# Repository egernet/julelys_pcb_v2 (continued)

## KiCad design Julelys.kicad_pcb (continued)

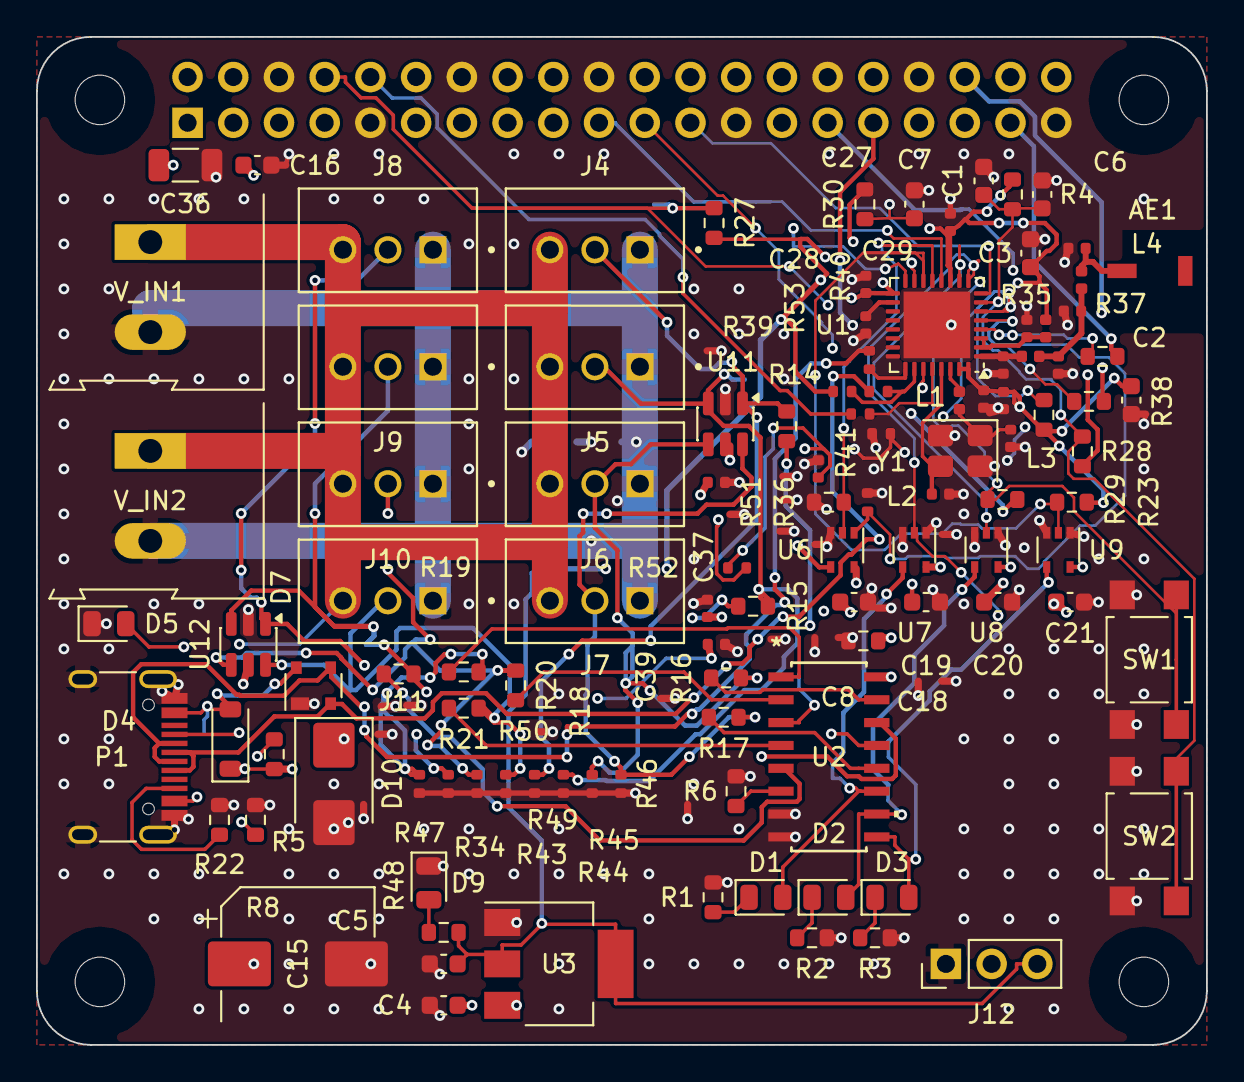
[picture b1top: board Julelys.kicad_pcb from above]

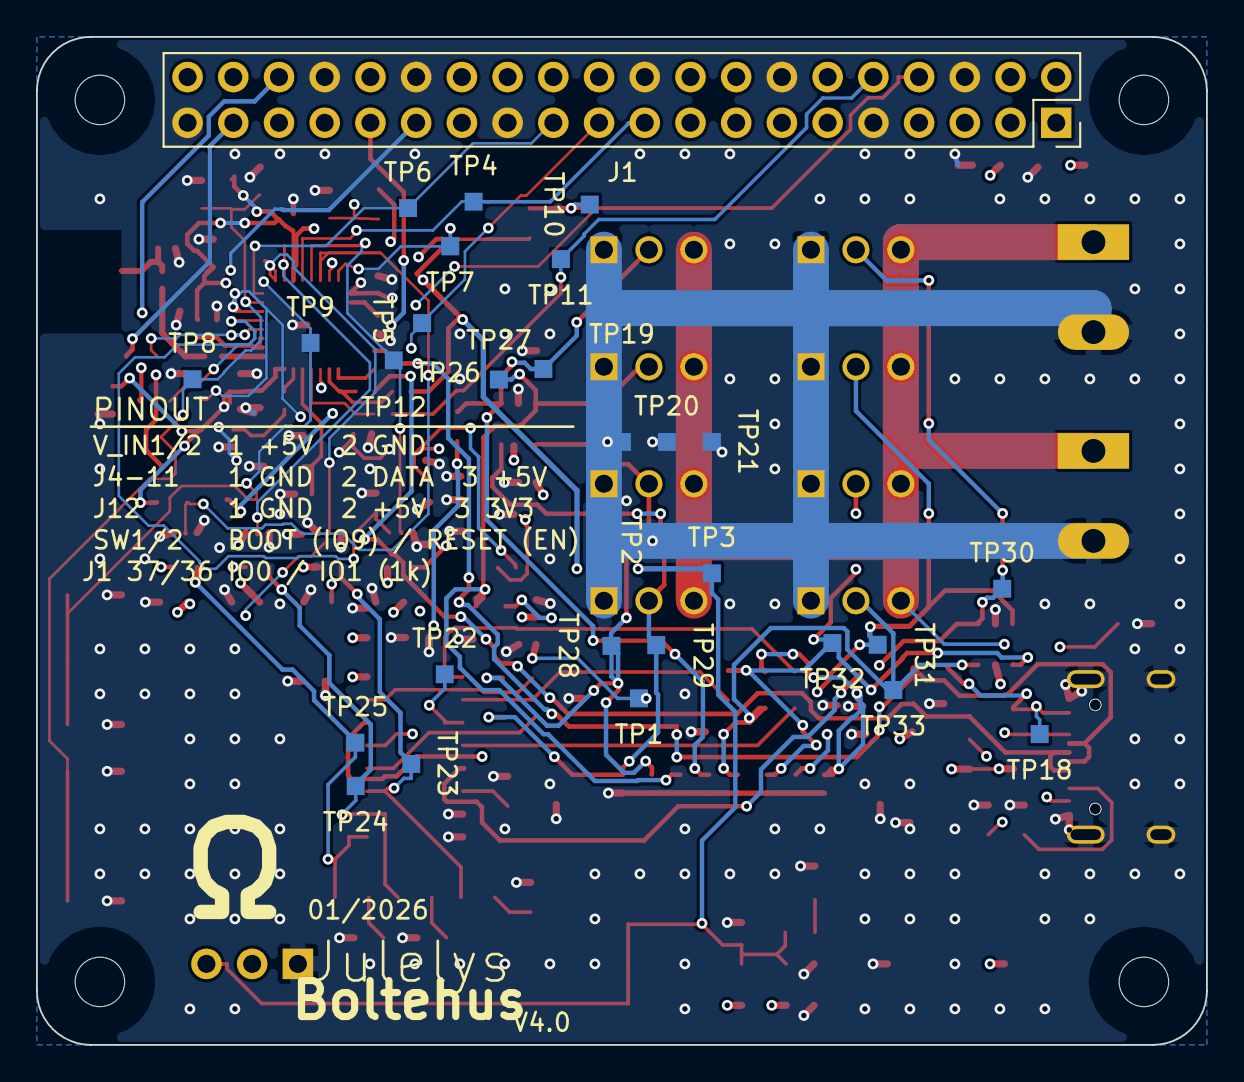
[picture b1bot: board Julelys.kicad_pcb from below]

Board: 4 copper layers, 65.0 x 56.0 mm, 142 parts (29 on the bottom side), 63 nets.

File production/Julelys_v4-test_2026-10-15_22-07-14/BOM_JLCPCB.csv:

Comment,Designator,Footprint,LCSC Part #
RFANT3216120A5T,AE1,Walsin_RFANT3216120A5T,C127629
1uf/16V,C1,0603,C15849
10uf,"C2,C4",0603,C96446
100nF,"C3,C6,C8,C16,C18,C19,C20,C21",0603,C14663
22uF,C5,0603,C59461
1nF,C7,0603,C1588
470uF,C15,CP_Elec_8x10,C164069
1uF,"C24,C25,C29",0402,C52923
10nF,"C26,C40",0402,C15195
100nF,"C27,C28,C37,C38,C39",0402,C1525
22pF,"C30,C31",0402,C1555
1.5pF,"C32,C33",0402,C1552
100uF,C36,1206,C15008
LED RED,"D1,D2,D3",0805,C84256
B5819W,D4,D_SOD-123,C8598
LED GREEN,"D5,D9",0805,C2297
SP0503BAHT,D7,SOT-143,C7074
SMBJ5.0A,D10,D_SMB,C19077558
2.0nH,L1,0402,C18216
24nH,L2,0402,C74301
2.7nH,L3,0402,C77108
6.8nH,L4,0402,C77110
USB_C_Receptacle_USB2.0,P1,USB_C_Receptacle_HRO_TYPE-C-31-M-12,C165948
1K,"R1,R2,R3,R28,R29,R34,R37,R38",0603,C21190
10K,"R4,R6,R23,R27,R30,R35,R36",0603,C25804
5.1k,"R5,R8,R22",0603,C23186
330,"R14,R15,R16,R17,R18,R19,R20,R21",0603,C23138
22,"R39,R40",0402,C25092
510,R42,0402,C25123
10k,"R43,R44,R45,R46,R47,R48,R49,R50,R51,R53",0402,C25744
15k,R52,0402,C25756
SW_Push,"SW1,SW2",SW_SPST_TL3305A,C2886899
ESP32-C3FH4,U1,QFN-32-1EP_5x5mm_P0.5mm_EP3.7x3.7mm,C2858491
74HC4051,U2,SOIC16_TOS,C9386
AMS1117-3.3,U3,SOT-223-3_TabPin2,C6186
74AHCT1G125,"U6,U7,U8,U9",SOT-353_SC-70-5,C350557
SRV05-4,"U11,U12",SOT-23-6,C7420376
40MHz,Y1,Crystal_SMD_3225-4Pin_3.2x2.5mm,C9010

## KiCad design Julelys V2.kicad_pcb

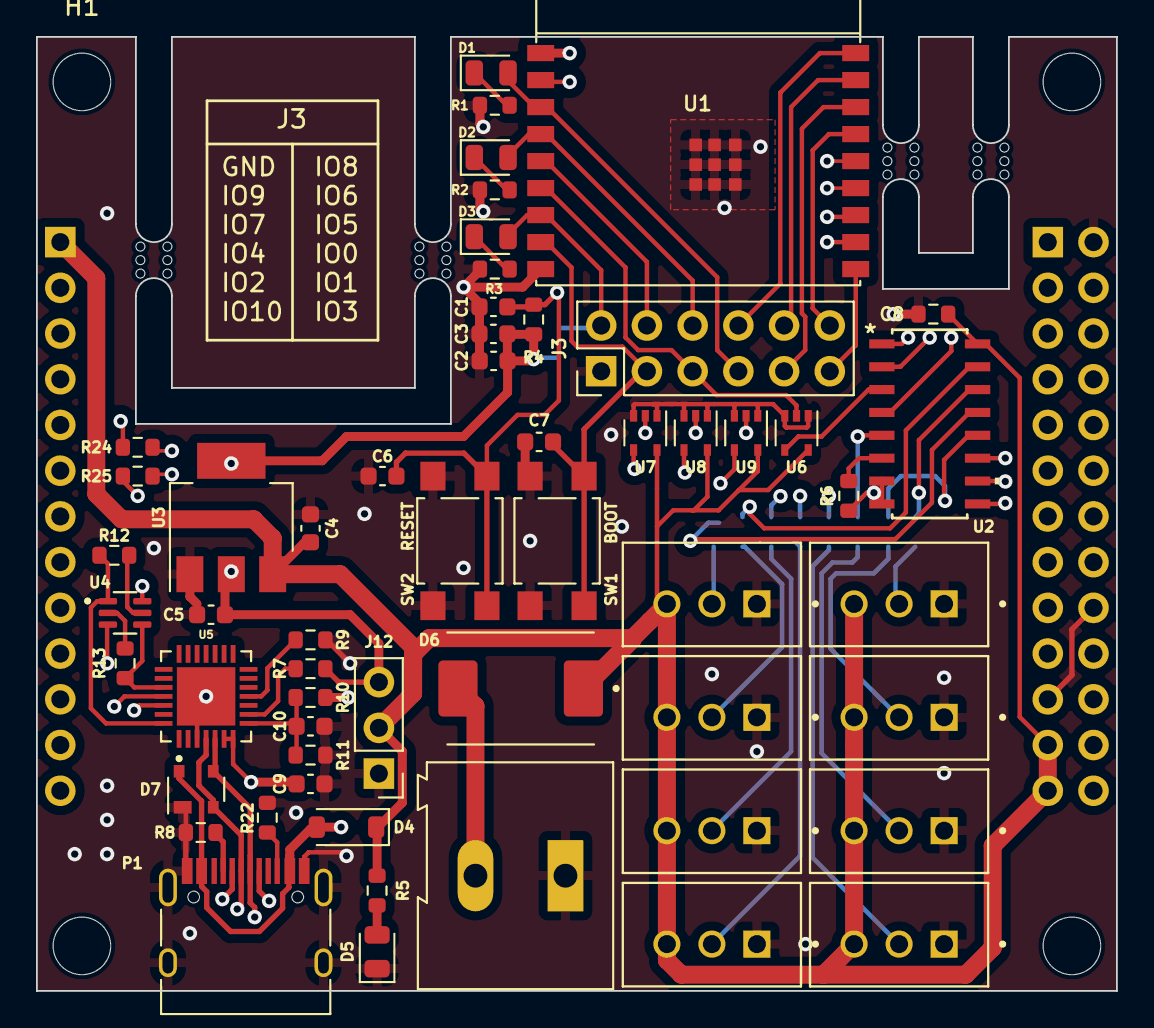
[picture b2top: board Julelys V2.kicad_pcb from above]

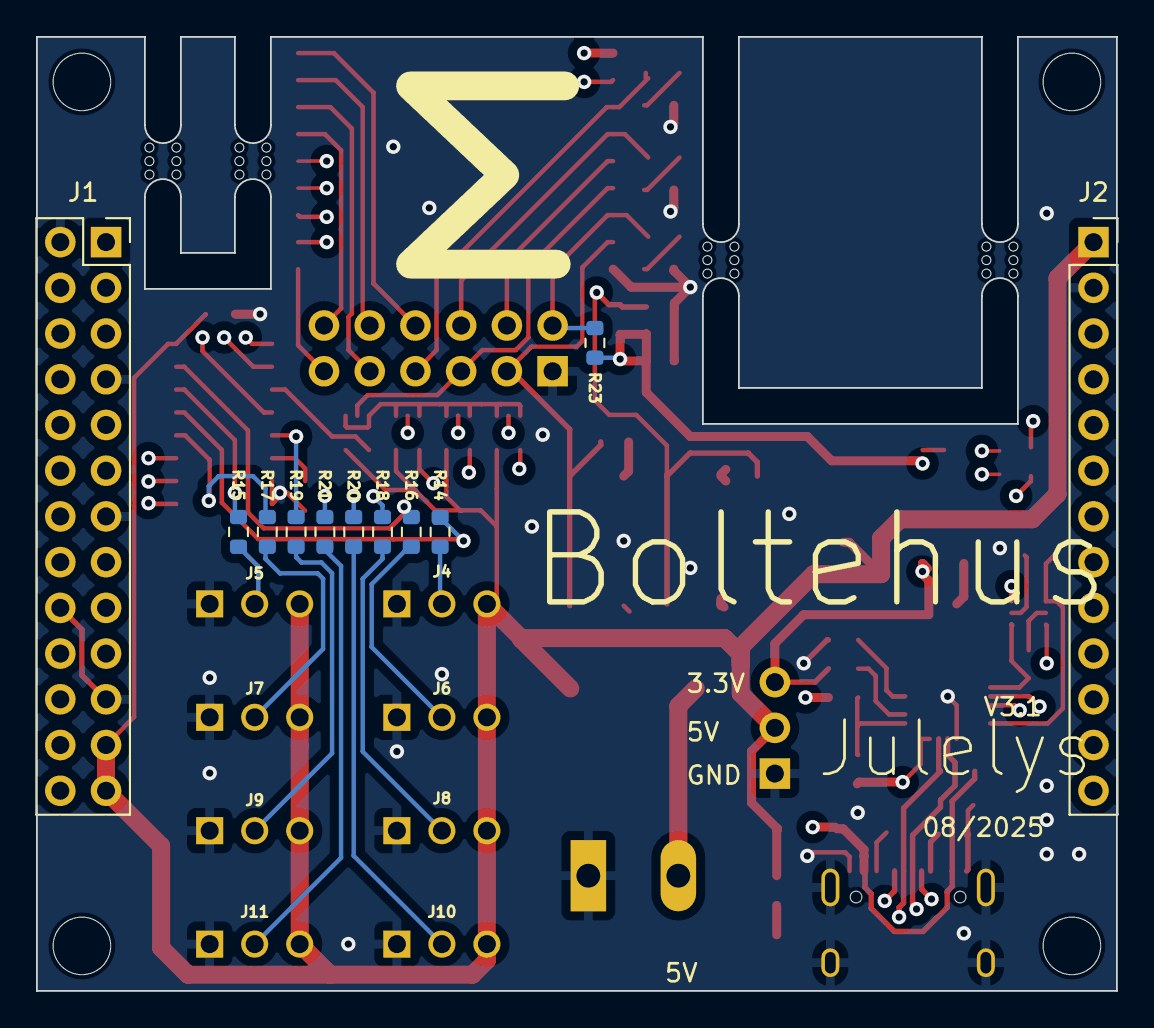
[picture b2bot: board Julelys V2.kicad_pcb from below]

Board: 4 copper layers, 60.0 x 53.0 mm, 75 parts (11 on the bottom side), 59 nets.

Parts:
C1: 1uf/16V; C_0603_1608Metric
C2, C4, C5: 10uf; C_0603_1608Metric
C3, C6, C7: 0.1uf; C_0603_1608Metric
C8: 100nf; R_0603_1608Metric
C9: 10uF/25V(20%); C_0603_1608Metric
C10: 1uF/16V(10%); C_0603_1608Metric
D1, D2, D3: LED RED; LED_0805_2012Metric
D4: 1N5819HW-7-F; D_SOD-123
D5: LED GREEN; LED_0805_2012Metric
D6: SS34-E3_57T; DIOM7959X262N
D7: SP0503BAHT; SOT-143
H1, H2, H3, H4: MountingHole; MountingHole_3.2mm_M3
J1: Conn_02x13_Top_Bottom; PinSocket_2x13_P2.54mm_Vertical
J2: Conn_01x13; PinSocket_1x13_P2.54mm_Vertical
J3: Conn_02x06_Odd_Even; PinHeader_2x06_P2.54mm_Vertical
J4, J5, J6, J7, J8, J9, J10, J11: B3B-XH-A; JST_B3B-XH-A
J12: Conn_01x03_Pin; PinHeader_1x03_P2.54mm_Vertical
P1: USB_C_Receptacle_USB2.0; USB_C_Receptacle_HRO_TYPE-C-31-M-12
R1, R2, R3: 270; R_0603_1608Metric
R4, R6, R9, R23: 10K; R_0603_1608Metric
R5: 5k1; R_0603_1608Metric
R7: 1K; R_0603_1608Metric
R8, R22: 5.1K; R_0603_1608Metric
R10: 22.1K; R_0603_1608Metric
R11: 47.5K; R_0603_1608Metric
R12, R13: 10k; R_0603_1608Metric
R14, R15, R16, R17, R18, R19, R20, R21: 330; R_0603_1608Metric
R24, R25: 22; R_0603_1608Metric
SW1, SW2: SW_Push; SW_SPST_TL3305A
U1: ESP32-C3-WROOM-02
U2: 74HC4051; SOIC16_TOS
U3: AMS1117-3.3; SOT-223-3_TabPin2
U4: BC847BDW1T1G; SOT65P210X110-6N
U5: CP2102N-A02-GQFN28; QFN50P500X500X80-29N
U6, U7, U8, U9: 74AHCT1G125; SOT-353_SC-70-5
V_IN1: 5V; TerminalBlock_Altech_AK300-2_P5.00mm
mouse-bite-2mm-slot, mouse-bite-2mm-slot#2, mouse-bite-2mm-slot#3, mouse-bite-2mm-slot#4: VAL**; mouse-bite-2mm-slot

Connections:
+3.3V: C2.1, C3.1, C5.1, C9.1, J12.3, R4.1, R7.2, R23.1, U1.1 (3V3), U3.2 (VO), U5.6 (VDD), U5.7 (VREGIN)
+5V: C4.1, C8.2, D4.1 (K), D6.C, J1.23, J1.25, J2.1, J4.3, J5.3, J6.3, J7.3, J8.3, J9.3, J10.3, J11.3, J12.2, R5.1, U2.16 (VCC), U3.3 (VI), U6.5 (VCC), U7.5 (VCC), U8.5 (VCC), U9.5 (VCC)
/AS0: U2.11 (S0), U7.4
/AS1: U2.10 (S1), U8.4
/AS2: U2.9 (S2), U9.4
/CH1: J4.2, R14.2
/CH2: J5.2, R15.2
/CH3: J6.2, R16.2
/CH4: J7.2, R17.2
/CH5: J8.2, R18.2
/CH6: J9.2, R19.2
/CH7: J10.2, R20.2
/CH8: J11.2, R21.2
/Data: U2.3 (A), U6.4
/MCH1: R14.1, U2.13 (A0)
/MCH2: R15.1, U2.14 (A1)
/MCH3: R16.1, U2.15 (A2)
/MCH4: R17.1, U2.12 (A3)
/MCH5: R18.1, U2.1 (A4)
/MCH6: R19.1, U2.5 (A5)
/MCH7: R20.1, U2.2 (A6)
/MCH8: R21.1, U2.4 (A7)
A0: D1.2 (A), J3.7, U1.3 (GPIO4/ADC1_CH4), U7.2
A1: D2.2 (A), J3.6, U1.4 (GPIO5/ADC2_CH0), U8.2
A2: D3.2 (A), J3.2, R23.2, U1.7 (GPIO8), U9.2
CHIP_UP: C1.1, C6.2, R4.2, SW2.2, U1.2 (EN/CHIP_PU), U4.6 (COLLECTOR2)
CLK: J1.4, J3.12, U1.15 (GPIO3/ADC1_CH3)
CS: J1.3, J3.11, U1.10 (GPIO10)
DTR: R12.2, U4.1 (EMITTER2), U5.28 (DTR)
GND: C1.2, C2.2, C3.2, C4.2, C5.2, C6.1, C7.1, C8.1, C9.2, C10.2, D5.1 (K), D7.1 (A), J1.2, J1.7, J1.13, J1.18, J1.21, J2.2, J3.1, J4.1, J5.1, J6.1, J7.1, J8.1, J9.1, J10.1, J11.1, J12.1, P1.A1 (GND), P1.A12 (GND), P1.B1 (GND), P1.B12 (GND), P1.S1 (SHIELD), R1.2, R2.2, R3.2, R6.2, R8.2, R9.2, R11.2, R22.2, SW1.1, SW2.1, U1.9 (GND), U1.19 (GND), U2.7 (VEE), U2.8 (GND), U3.1 (GND), U5.3 (GND), U5.29 (GND__1), U6.1, U6.3 (GND), U7.1, U7.3 (GND), U8.1, U8.3 (GND), U9.1, U9.3 (GND), V_IN1.1
IO0: J3.8, U1.18 (GPIO0/ADC1_CH0/XTAL_32K_P)
IO1: J3.10, U1.17 (GPIO1/ADC1_CH1/XTAL_32K_N)
IO2: J1.6, J3.9, U1.16 (GPIO2/ADC1_CH2)
IO6: J1.8, J3.4, U1.5 (GPIO6)
IO7: J3.5, U1.6 (GPIO7), U6.2
IO9: C7.2, J3.3, SW1.2, U1.8 (GPIO9), U4.3 (COLLECTOR1)
unnamed: D1.1 (K), R1.1
unnamed: D2.1 (K), R2.1
unnamed: D3.1 (K), R3.1
unnamed: D5.2 (A), R5.2
unnamed: J2.3, R24.2
unnamed: J2.4, R25.2
unnamed: P1.A5 (CC1), R8.1
unnamed: P1.B5 (CC2), R22.1
unnamed: R6.1, U2.6 (~E)
unnamed: R12.1, U4.5 (BASE1)
unnamed: R13.2, U4.2 (BASE2)
unnamed: D7.2 (K), P1.A6 (D+), P1.B6 (D+), U5.4 (D+)
unnamed: D7.3 (K), P1.A7 (D-), P1.B7 (D-), U5.5 (D-)
unnamed: C10.1, R10.2, R11.1, U5.8 (VBUS)
unnamed: R7.1, U5.9 (~RST)
unnamed: R9.1, U5.11 (~SUSPEND)
unnamed: D6.A, V_IN1.2
RTS: R13.1, U4.4 (EMITTER1), U5.24 (RTS)
RXD: J1.19, U1.11 (GPIO20/U0RXD), U5.26 (TXD)
TXD: J1.17, U1.12 (GPIO21/U0TXD), U5.25 (RXD)
USB_D+: R25.1, U1.14 (GPIO19/USB_D+)
USB_D-: R24.1, U1.13 (GPIO18/USB_D-)
VBUS: D4.2 (A), D7.4 (K), P1.A4 (VBUS), P1.A9 (VBUS), P1.B4 (VBUS), P1.B9 (VBUS), R10.1

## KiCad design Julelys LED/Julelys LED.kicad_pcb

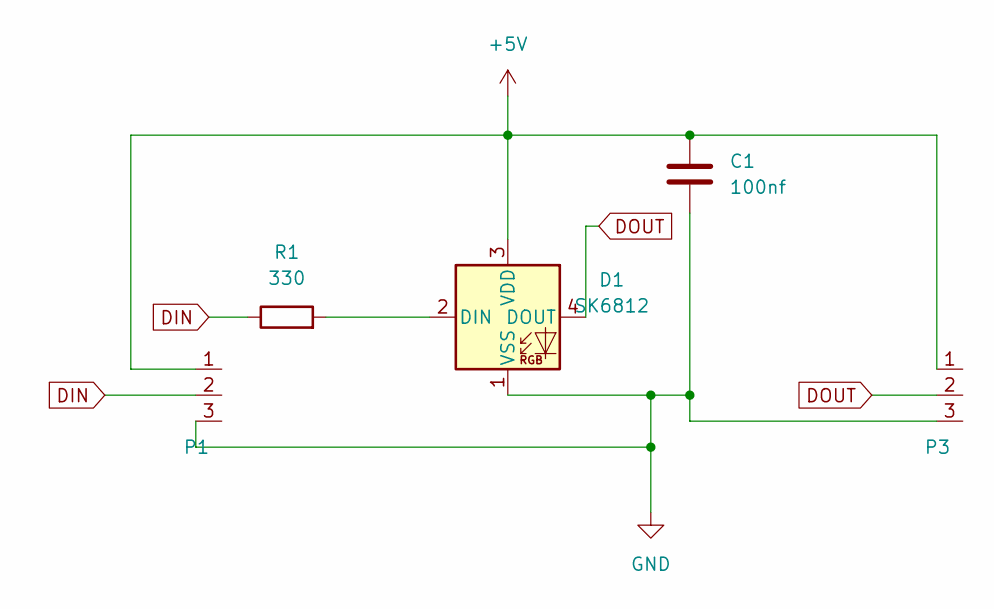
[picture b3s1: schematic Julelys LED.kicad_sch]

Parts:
C1: 100nf; C_0603_1608Metric
D1: SK6812; LED_SK6812_PLCC4_5.0x5.0mm_P3.2mm
P1, P3: Solder Pads 3x2.54
R1: 330; R_0603_1608Metric

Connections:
+5V: C1.1, D1.3 (VDD), P1.1, P3.1
DIN: P1.2, R1.1
DOUT: D1.4 (DOUT), P3.2
GND: C1.2, D1.1 (VSS), P1.3, P3.3
unnamed: D1.2 (DIN), R1.2

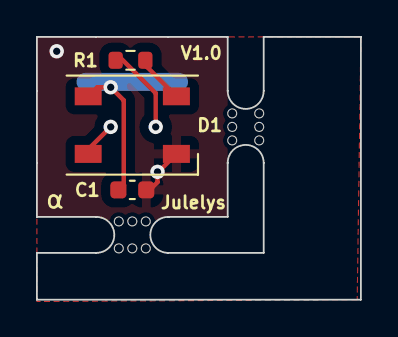
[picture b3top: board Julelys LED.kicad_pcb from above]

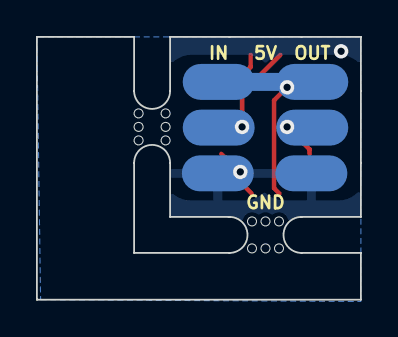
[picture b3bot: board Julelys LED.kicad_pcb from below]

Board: 4 copper layers, 18.0 x 14.6 mm, 7 parts (2 on the bottom side), 5 nets.

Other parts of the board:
mouse-bite-2mm-slot, mouse-bite-2mm-slot#2: VAL**; mouse-bite-2mm-slot

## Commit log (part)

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2024-01-11 Add files to PCB v2
2024-04-09 clean up
2025-07-21 version 3
2025-07-26 LEDs
2025-07-31 fix bugs
2025-08-30 Small update
2025-08-30 rename
2025-08-30 Upate
2025-12-26 Add claude
2025-12-28 Begin next step
2025-12-28 more to next step
